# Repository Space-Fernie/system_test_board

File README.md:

# system_test_board
Test board for the Arietta G25 system

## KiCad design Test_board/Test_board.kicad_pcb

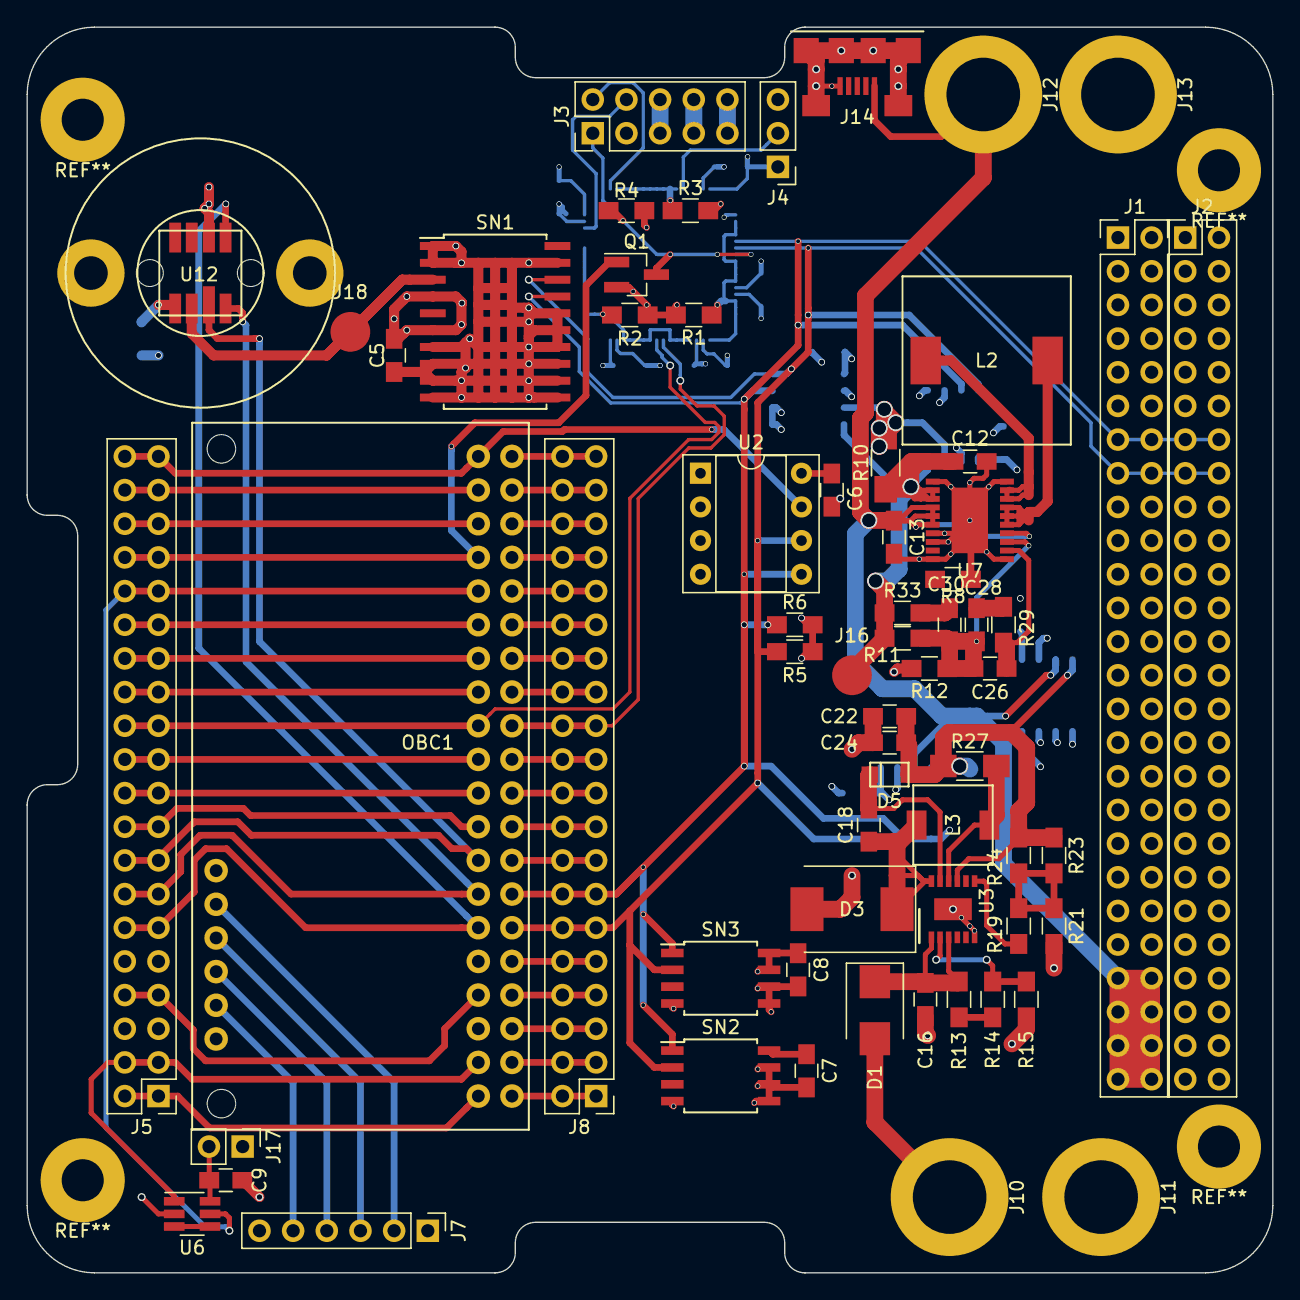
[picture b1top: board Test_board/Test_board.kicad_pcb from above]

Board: 4 copper layers, 94.0 x 94.0 mm, 80 parts (0 on the bottom side), 74 nets.

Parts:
C1, C2, C3, C4, C5, C6, C7, C8, C9, C14, C15, C16, C20, C21, C32, C33: 0.1uF; C_0805_HandSoldering
C12, C24: 100uF; C_0805_HandSoldering
C13: 47uF; C_0805_HandSoldering
C18: 1uF; C_0805_HandSoldering
C22: 10uF; C_0805_HandSoldering
C26: 12pF; C_0805_HandSoldering
C28: 680pF; C_0805_HandSoldering
C30: 47pF; C_0805_HandSoldering
D1: MBRS140; D_SMB
D3: MBRS340; D_SMC
D5: D; SOD-123FL
J1, J2: CONN_02X26; Pin_Header_Straight_2x26_Pitch2.54mm
J3: Conn_02x05_Odd_Even; Pin_Header_Straight_2x05_Pitch2.54mm
J4: Conn_01x03; Pin_Header_Straight_1x03_Pitch2.54mm
J5, J8: Conn_02x20_Odd_Even; Pin_Header_Straight_2x20_Pitch2.54mm
J7: Conn_01x06; Pin_Header_Straight_1x06_Pitch2.54mm
J10, J11, J12, J13: 4.19mmBananaJack; 4.19Banana
J14: USB_OTG; micro_usb_smd
J16, J18: TEST_1P; Measurement_Point_Round-SMD-Pad_Big
J17: Conn_01x02; Pin_Header_Straight_1x02_Pitch2.54mm
L2: 2.2uH; L-7443330220
L3: 6.8uH; L-SLF6028T-6R8M1R5-PF
OBC1: Arietta_G25
Q1: Q_NMOS_GSD; SOT-23_Handsoldering
R1, R2, R3: 4k7; R_0805_HandSoldering
R4: 4K7; R_0805_HandSoldering
R5, R6: 1k; R_0805_HandSoldering
R8: 90.9k; R_0805_HandSoldering
R9, R10: 20m; R_1206_HandSoldering
R11: 825k; R_0805_HandSoldering
R12: 182k; R_0805_HandSoldering
R13, R14, R15: 100k; R_0805_HandSoldering
R19: 179k; R_0805_HandSoldering
R21: 330k; R_0805_HandSoldering
R23, R24: 180k; R_0805_HandSoldering
R27: 50m; R_1206_HandSoldering
R29: 49.9k; R_0805_HandSoldering
R33: 6.49k; R_0805_HandSoldering
SN1: DS3232; SOIC-20W_7.5x12.8mm_Pitch1.27mm
SN2, SN3: DS1624; SOIJ-8_5.3x5.3mm_Pitch1.27mm
U1: STM32F303RE; LQFP-64_10x10mm_Pitch0.5mm
U2: 24LC256; DIP-8_W7.62mm_Socket
U3: LT3652; 12MSOP-E
U4, U9, U10, U11: INA219; SOIC-8_3.9x4.9mm_Pitch1.27mm
U6: MAX6730A; SOT-23-6_Handsoldering
U7: LTC3113; 20TSSOP-E
U12: MS5540C

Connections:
+3V3: C1.1, C2.1, C3.1, C4.1, C5.1, C6.1, C7.1, C8.1, C14.2, C15.2, C20.2, C21.2, C32.1, C33.1, J1.1, J1.2, J1.3, J1.4, J1.5, J1.6, J1.7, J1.8, J3.7, J3.8, J4.1, J5.5, J5.6, J7.6, J17.1, OBC1.5, OBC1.DP1, R4.1, R5.2, R6.2, R10.2, SN1.4, SN1.6, SN2.8, SN3.7, SN3.8, U1.13, U1.19, U1.32, U1.48, U1.64, U2.8, U4.5, U4.7, U9.5, U10.2, U10.5, U11.2, U11.5, U11.7, U12.5
+5V: J3.9, J3.10
+BATT: C13.1, J1.45, J1.46, J1.47, J1.48, J1.49, J1.50, J1.51, J1.52, J12.1, J14.1, R9.2, U7.4, U7.5, U7.6, U7.14, U9.7, U10.7
/32kHz: J18.1, SN1.3, U12.6
/ARM_MSTR_RST: J5.33, J5.34, OBC1.33, Q1.1
/ARM_RST: J3.1, Q1.3, R4.2, U1.7
/ARM_SWCLK: J3.2, U1.49
/ARM_SWDIO: J3.4, U1.46
/BARO_CLK: J5.11, J5.12, OBC1.11, U12.1
/BARO_MISO: J5.13, J5.14, OBC1.13, U12.8
/BARO_MOSI: J5.15, J5.16, OBC1.15, U12.7
/B_MCU_GND: R2.1, U1.20, U1.21, U1.22, U1.23, U1.26, U1.27, U1.28, U1.29, U1.30, U1.33, U1.34, U1.35, U1.36, U1.37, U1.38, U1.39, U1.40, U1.41, U1.42, U1.43, U1.44, U1.45
/DBG_MISO: J7.4, OBC1.DP3
/DBG_MOSI: J7.3, OBC1.DP4
/EEPROM_WP: J5.39, J5.40, OBC1.39, U2.7
/L_MCU_GND: R1.1, U1.2, U1.3, U1.4, U1.8, U1.9, U1.10, U1.11, U1.14, U1.15, U1.16, U1.17
/POWER/MPPT_IN: D1.2, J10.1
/POWER/MPPT_OUT: C22.1, C24.1, D5.2, R9.1, R23.1, R24.1, R27.1, U3.9, U9.8, U10.8
/POWER/VOUT3: C12.1, J16.1, R10.1, R11.1, R33.1, U4.8, U7.2, U7.3, U11.8
/SCL0: J1.15, J1.16, J2.15, J2.16, J8.11, J8.12, OBC1.12, R5.1, SN1.18, SN1.20, SN2.2, SN3.2, U1.6, U2.6, U4.4, U9.4, U10.4, U11.4
/SDA0: J1.13, J1.14, J2.13, J2.14, J8.13, J8.14, OBC1.14, R6.1, SN1.17, SN2.1, SN3.1, U1.5, U2.5, U4.3, U9.3, U10.3, U11.3
/T_MCU_GND: R3.1, U1.50, U1.51, U1.52, U1.53, U1.54, U1.55, U1.56, U1.57, U1.58, U1.59, U1.61, U1.62
/UART0_MISO: J8.23, J8.24, OBC1.24, U1.24
/UART0_MOSI: J5.23, J5.24, OBC1.23, U1.25
/WDT_KICK: J5.31, J5.32, OBC1.31, U6.5
/~OBC_RST: J5.3, J5.4, OBC1.3, U6.1
GND: C1.2, C2.2, C3.2, C4.2, C5.2, C6.2, C7.2, C8.2, C9.2, C12.2, C13.2, C14.1, C15.1, C16.2, C20.1, C21.1, C22.2, C24.2, C32.2, C33.2, D3.2, J1.18, J1.20, J1.22, J1.24, J1.26, J1.28, J1.30, J1.31, J1.32, J1.34, J1.36, J1.37, J1.38, J2.1, J2.2, J2.3, J2.4, J2.5, J2.6, J2.7, J2.8, J2.45, J2.46, J2.47, J2.48, J2.49, J2.50, J2.51, J2.52, J3.5, J3.6, J4.3, J5.9, J5.10, J7.1, J11.1, J13.1, J14.5, J14.6, OBC1.9, OBC1.DP6, Q1.2, R1.2, R2.2, R3.2, R8.2, R12.2, R15.2, R21.2, SN1.1, SN1.2, SN1.7, SN1.8, SN1.9, SN1.10, SN1.11, SN1.12, SN1.13, SN1.14, SN1.15, SN1.16, SN1.19, SN2.4, SN2.5, SN2.6, SN2.7, SN3.4, SN3.5, SN3.6, U1.1, U1.12, U1.18, U1.31, U1.47, U1.63, U2.1, U2.2, U2.3, U2.4, U3.6, U3.13, U4.1, U4.2, U4.6, U6.2, U7.1, U7.7, U7.8, U7.10, U7.11, U7.20, U7.21, U9.1, U9.2, U9.6, U10.1, U10.6, U11.1, U11.6, U12.2
unnamed: C9.1, J17.2, U6.6
unnamed: C16.1, D1.1, R13.1, U3.1, U3.3
unnamed: C18.1, D3.1, L3.2, U3.12
unnamed: C18.2, D5.1, U3.11
unnamed: C26.1, C28.1, C30.2, R11.2, R12.1, U7.13
unnamed: C26.2, R29.2, U7.12
unnamed: C28.2, R29.1
unnamed: C30.1, R33.2
unnamed: J4.2, U1.60
unnamed: J5.1, J5.2, OBC1.1
unnamed: J5.7, J5.8, OBC1.7
unnamed: J5.17, J5.18, OBC1.17
unnamed: J5.19, J5.20, OBC1.19
unnamed: J5.21, J5.22, OBC1.21
unnamed: J5.25, J5.26, OBC1.25
unnamed: J5.27, J5.28, OBC1.27
unnamed: J5.29, J5.30, OBC1.29
unnamed: J5.35, J5.36, OBC1.35
unnamed: J5.37, J5.38, OBC1.37
unnamed: J7.2, OBC1.DP5
unnamed: J7.5, OBC1.DP2
unnamed: J8.1, J8.2, OBC1.2
unnamed: J8.3, J8.4, OBC1.4
unnamed: J8.5, J8.6, OBC1.6
unnamed: J8.7, J8.8, OBC1.8
unnamed: J8.9, J8.10, OBC1.10
unnamed: J8.15, J8.16, OBC1.16
unnamed: J8.17, J8.18, OBC1.18
unnamed: J8.19, J8.20, OBC1.20
unnamed: J8.21, J8.22, OBC1.22
unnamed: J8.25, J8.26, OBC1.26
unnamed: J8.27, J8.28, OBC1.28
unnamed: J8.29, J8.30, OBC1.30
unnamed: J8.31, J8.32, OBC1.32
unnamed: J8.33, J8.34, OBC1.34
unnamed: J8.35, J8.36, OBC1.36
unnamed: J8.37, J8.38, OBC1.38
unnamed: J8.39, J8.40, OBC1.40
unnamed: L2.1, U7.18, U7.19
unnamed: L2.2, U7.15, U7.16, U7.17
unnamed: L3.1, R27.2, U3.10
unnamed: R8.1, U7.9
unnamed: R13.2, R14.1
unnamed: R14.2, R15.1, U3.2
unnamed: R19.1, R21.1, R23.2, R24.2
unnamed: R19.2, U3.7
unnamed: U6.3, U6.4

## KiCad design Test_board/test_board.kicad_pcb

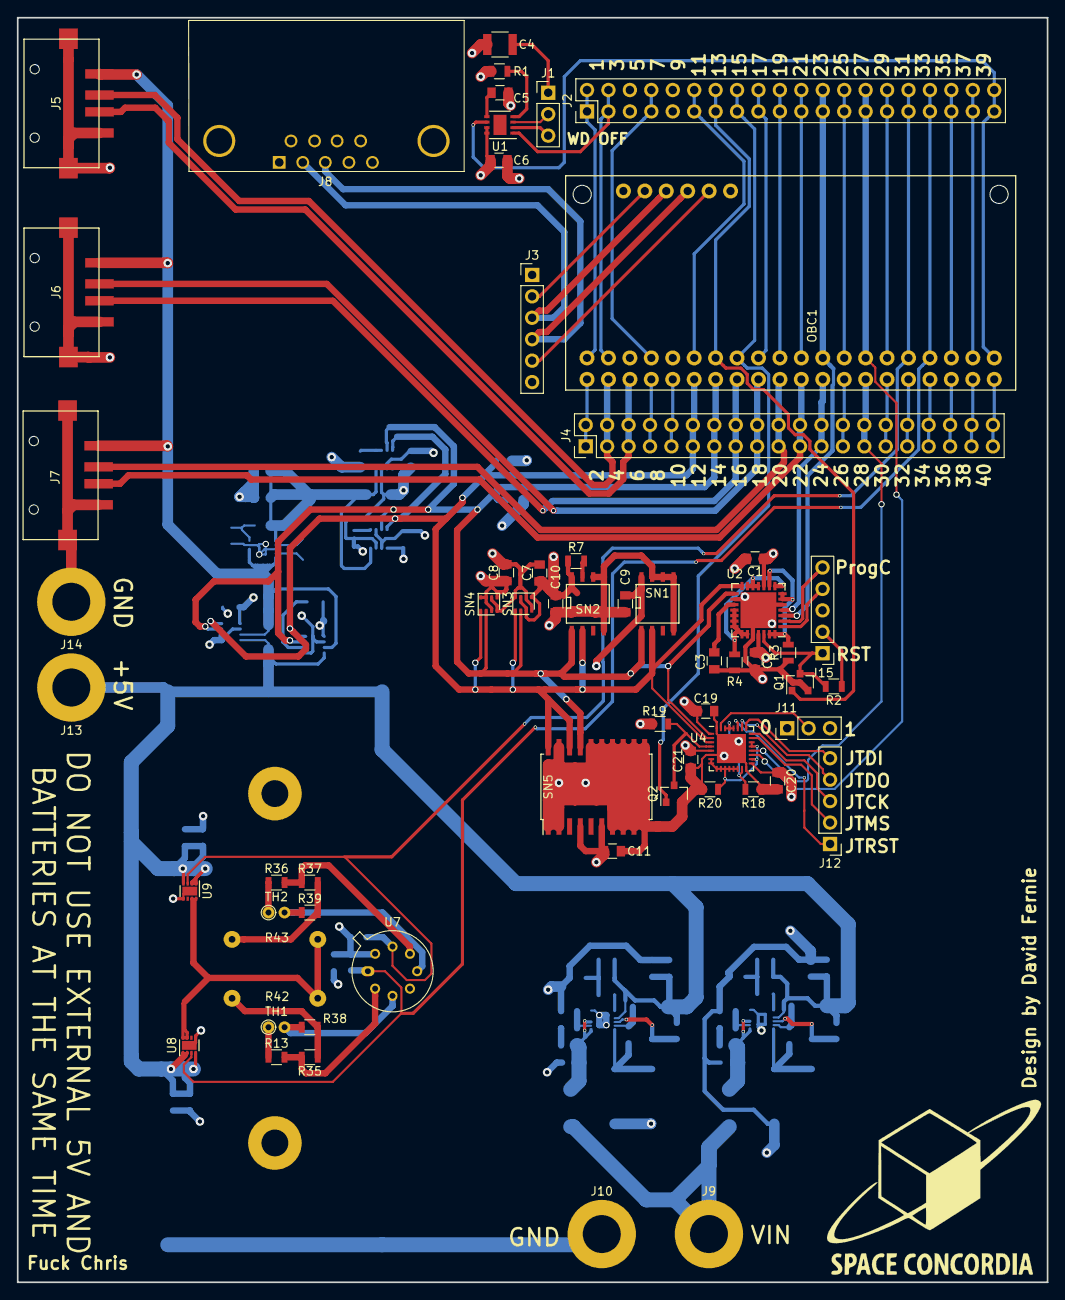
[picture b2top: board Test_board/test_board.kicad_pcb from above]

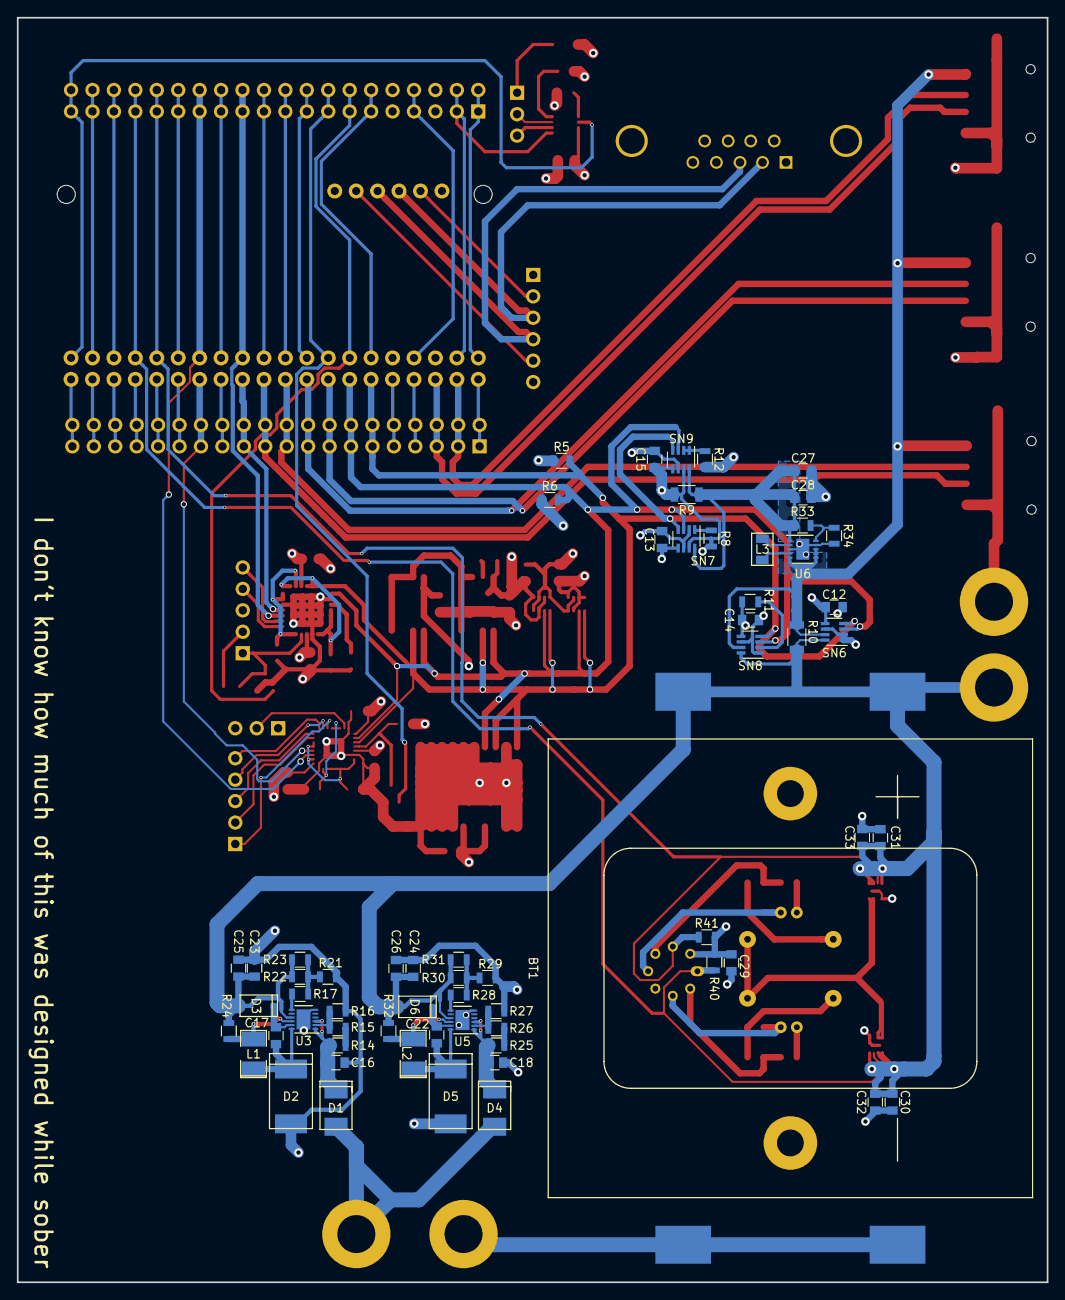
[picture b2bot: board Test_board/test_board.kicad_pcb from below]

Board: 4 copper layers, 122.0 x 149.9 mm, 124 parts (63 on the bottom side), 95 nets.

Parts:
BT1: Battery; Battery_Bracket_Small
C1, C2, C6, C7, C8, C9, C10, C11, C12, C13, C14, C15, C19, C20, C21, C29, C30, C31: 0.1uF; C_0805
C3, C16, C18, C23, C24: 10uF; C_0805
C4: 18uF; C_1210
C5: 0.2uF; C_0805
C17, C22, C32, C33: 1uF; C_0805
C25, C26: 100uF; C_0805
C27, C28: 22uF; C_0805
D1, D4: MBRS140; DO-214AA
D2, D5: MBRS340; SMC
D3, D6: D; SOD-323FL
J1, J11: CONN_01X03_MALE; Pin_Header_Straight_1x03_Pitch2.54mm
J2, J4: CONN_02X20; Pin_Header_Straight_2x20_Pitch2.54mm
J3: CONN_01X06; Pin_Header_Straight_1x06_Pitch2.54mm
J5, J6, J7: USB_A; USB_A_Board
J8: DB9_FEMALE; DB9FC
J9, J10, J13, J14: 4.19mmBananaJack; 4.19Banana
J12, J15: CONN_01X05; Pin_Header_Straight_1x05_Pitch2.54mm
L1, L2: 6.8uH; SMD-1210_Pol
L3: 1.5uH; SMD-1008
OBC1: Arietta_G25
Q1, Q2: 2N7002; SOT-23
R1, R33: 1M; R_0805
R2, R3, R4, R5, R6, R7, R8, R11, R12, R18, R19, R20, R40, R41: 4k7; R_0805
R9, R10: 20m; R_1206
R13, R35, R36, R37, R38, R39: 21k; R_0805
R14, R15, R16, R25, R26, R27: 100k; R_0805
R17, R28: 179k; R_0805
R21, R29: 330k; R_0805
R22, R23, R30, R31: 180k; R_0805
R24, R32: 50m; R_0805
R34: 178k; R_0805
R42, R43: HAP6948; WireConnection_0.80mmDrill
SN1, SN2: DS1624; SOIC-8-N
SN3, SN4: BMP280LGA; BMP280
SN5: DS3232; SOIC-20W_7.5x12.8mm_Pitch1.27mm
SN6, SN7, SN8, SN9: INA219; SOT-23-8
TH1, TH2: PT103J2; R_Axial_DIN0204_L3.6mm_D1.6mm_P1.90mm_Vertical
U1: MAX16056; DFN-8-1EP_3x3mm_Pitch0.65mm
U2: PIC24HJ128GP502-I/MM; QFN-28-1EP_6x6mm_Pitch0.65mm
U3, U5: LT3652; DFN-12-1EP_3x3mm_Pitch0.45mm
U4: STM32F302K8U6; QFN-32-1EP_5x5mm_Pitch0.5mm
U6: TPS63000; DFN-10-1EP_3x3mm_Pitch0.5mm
U7: LM193; TO-99-8_Window
U8, U9: TPS22965-Q1; DFN-8-1EP_2x2mm_Pitch0.5mm

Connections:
+3V3: C1.1, C2.1, C6.1, C7.1, C8.1, C9.1, C10.1, C11.1, C12.1, C13.1, C14.1, C15.1, C19.1, C20.1, C21.1, C29.2, J2.5, J2.6, J3.1, J11.3, J15.2, OBC1.5, OBC1.DP1, R1.1, R2.1, R5.1, R6.1, R7.1, R8.2, R9.2, R11.2, R12.2, R13.1, R19.2, R36.1, R40.1, R41.1, SN1.8, SN2.8, SN3.2, SN3.6, SN3.8, SN4.2, SN4.5, SN4.6, SN4.8, SN5.4, SN5.6, SN6.5, SN7.5, SN7.7, SN8.5, SN9.5, SN9.7, TH1.1, TH2.1, U1.7, U1.8, U2.10, U2.25, U4.1, U4.5, U4.17, U7.8
+BATT: BT1.1, C23.1, C24.1, C25.1, C26.1, C30.1, C31.1, C32.1, C33.1, D3.2, D6.2, J13.1, R10.1, R22.1, R23.1, R24.1, R30.1, R31.1, R32.1, SN6.8, SN8.8, U3.9, U5.9, U8.1, U8.2, U8.4, U9.1, U9.2, U9.4
/Arm_RST: J2.15, J2.16, OBC1.15, Q2.1
/DB_RX: J3.4, J8.3, OBC1.DP4
/DB_TX: J3.3, J8.2, OBC1.DP3
/JTCK: J12.3, U4.24
/JTDI: J12.5, U4.25
/JTDO: J12.4, U4.26
/JTMS: J12.2, U4.23
/JTRST: J12.1, U4.27
/M4_BOOT: J11.2, U4.31
/PIC_RST: J2.13, J2.14, OBC1.13, Q1.1
/Power/VCCP: D1.2, D4.2, J9.1
/ProgC: J15.5, U2.2
/ProgD: J15.4, U2.1
/Serial0_MISO: J4.23, J4.24, OBC1.24, U2.4
/Serial0_MOSI: J2.23, J2.24, OBC1.23, U2.3
/Serial1_MISO: J2.27, J2.28, OBC1.27, U4.19
/Serial1_MOSI: J4.27, J4.28, OBC1.28, U4.20
/USBA_D+: J4.5, J4.6, J5.3, OBC1.6
/USBA_D-: J4.3, J4.4, J5.2, OBC1.4
/USBB_D+: J4.15, J4.16, J6.3, OBC1.16
/USBB_D-: J4.17, J4.18, J6.2, OBC1.18
/USBC_D+: J4.21, J4.22, J7.3, OBC1.22
/USBC_D-: J4.19, J4.20, J7.2, OBC1.20
/Watchdog_pet: J2.39, J2.40, OBC1.39, U1.6
/~MCU_Reset: J15.1, Q1.3, R2.2, U2.26
/~RESET: J2.3, J2.4, OBC1.3, U1.1
GND: BT1.2, C1.2, C2.2, C3.2, C4.2, C5.2, C6.2, C7.2, C8.2, C9.2, C10.2, C11.2, C12.2, C13.2, C14.2, C15.2, C16.2, C18.2, C19.2, C20.2, C21.2, C23.2, C24.2, C25.2, C26.2, C27.2, C28.2, C29.1, C30.2, C31.2, C32.2, C33.2, D2.2, D5.2, J1.3, J2.9, J2.10, J3.6, J5.4, J5.5, J6.4, J6.5, J7.4, J7.5, J10.1, J11.1, J14.1, J15.3, OBC1.9, OBC1.DP6, Q1.2, Q2.2, R3.1, R4.2, R16.2, R18.2, R20.2, R21.1, R27.2, R29.1, R34.2, R35.2, R37.2, R38.2, R39.2, R42.2, R43.2, SN1.4, SN1.5, SN1.6, SN1.7, SN2.4, SN2.5, SN2.6, SN3.1, SN3.5, SN3.7, SN4.1, SN4.7, SN5.1, SN5.2, SN5.7, SN5.8, SN5.9, SN5.10, SN5.11, SN5.12, SN5.13, SN5.14, SN5.15, SN5.16, SN5.19, SN6.1, SN6.2, SN6.6, SN7.2, SN7.6, SN8.1, SN8.6, SN9.6, U1.2, U2.5, U2.16, U2.24, U2.29, U3.6, U3.13, U4.6, U4.16, U4.32, U4.33, U5.6, U5.13, U6.3, U6.9, U6.11, U7.4, U8.5, U8.9, U9.5, U9.9
Heater1: J2.33, J2.34, OBC1.33, R40.2, U7.1, U8.3
Heater2: J2.31, J2.32, OBC1.31, R41.2, U7.7, U9.3
unnamed: C3.1, U2.17
unnamed: C4.1, J1.1
unnamed: C5.1, U1.5
unnamed: C16.1, D1.1, R14.1, U3.1, U3.3
unnamed: C17.1, D3.1, U3.11
unnamed: C17.2, D2.1, L1.1, U3.12
unnamed: C18.1, D4.1, R25.1, U5.1, U5.3
unnamed: C22.1, D6.1, U5.11
unnamed: C22.2, D5.1, L2.1, U5.12
unnamed: J1.2, U1.3
unnamed: J2.1, J2.2, OBC1.1
unnamed: J2.7, J2.8, OBC1.7
unnamed: J2.11, J2.12, OBC1.11
unnamed: J2.17, J2.18, OBC1.17
unnamed: J2.19, J2.20, OBC1.19
unnamed: J2.21, J2.22, OBC1.21
unnamed: J2.25, J2.26, OBC1.25
unnamed: J2.29, J2.30, OBC1.29
unnamed: J2.35, J2.36, OBC1.35
unnamed: J2.37, J2.38, OBC1.37
unnamed: J3.2, OBC1.DP2
unnamed: J3.5, OBC1.DP5
unnamed: J4.1, J4.2, OBC1.2
unnamed: J4.7, J4.8, OBC1.8
unnamed: J4.9, J4.10, OBC1.10
unnamed: J4.25, J4.26, OBC1.26
unnamed: J4.29, J4.30, OBC1.30
unnamed: J4.31, J4.32, OBC1.32
unnamed: J4.33, J4.34, OBC1.34
unnamed: J4.35, J4.36, OBC1.36
unnamed: J4.37, J4.38, OBC1.38
unnamed: J4.39, J4.40, OBC1.40
unnamed: L1.2, R24.2, U3.10
unnamed: L2.2, R32.2, U5.10
unnamed: L3.1, U6.4
unnamed: L3.2, U6.2
unnamed: Q2.3, R19.1, U4.4
unnamed: R1.2, U1.4
unnamed: R3.2, U2.6, U2.7, U2.9, U2.27, U2.28
unnamed: R4.1, U2.8, U2.11, U2.12, U2.13, U2.18, U2.19, U2.20, U2.21, U2.22, U2.23
unnamed: R7.2, SN2.7
unnamed: R8.1, SN7.1
unnamed: R11.1, SN8.2
unnamed: R12.1, SN9.1, SN9.2
unnamed: R13.2, R35.1, U7.2
unnamed: R14.2, R15.1
unnamed: R15.2, R16.1, U3.2
unnamed: R17.1, R21.2, R22.2, R23.2
unnamed: R17.2, U3.7
unnamed: R18.1, U4.15, U4.28, U4.29, U4.30
unnamed: R20.1, U4.7, U4.8, U4.9, U4.10, U4.11, U4.12, U4.13, U4.14, U4.18, U4.21, U4.22
unnamed: R25.2, R26.1
unnamed: R26.2, R27.1, U5.2
unnamed: R28.1, R29.2, R30.2, R31.2
unnamed: R28.2, U5.7
unnamed: R33.2, R34.1, U6.10
unnamed: R36.2, R37.1, U7.6
unnamed: R38.1, TH1.2, U7.3
unnamed: R39.1, TH2.2, U7.5
unnamed: R42.1, R43.1, U8.7, U8.8, U9.7, U9.8
SCL0: J4.11, J4.12, OBC1.12, R5.2, SN1.2, SN2.2, SN3.4, SN4.4, SN5.18, SN5.20, SN6.4, SN7.4, SN8.4, SN9.4, U2.14, U4.3
SDA0: J4.13, J4.14, OBC1.14, R6.2, SN1.1, SN2.1, SN3.3, SN4.3, SN5.17, SN6.3, SN7.3, SN8.3, SN9.3, U2.15, U4.2
VCC: J5.1, J6.1, J7.1, R10.2, SN6.7, SN8.7, U6.5, U6.6, U6.7, U6.8
VDD: C27.1, C28.1, R9.1, R33.1, SN7.8, SN9.8, U6.1

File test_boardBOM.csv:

"Id,""Designator"",""Package"",""Quantity"",""Designation"",""Supplier and ref"",",,,,,,,,,,,,,,,,,
"1,""J5,J6,J7"",""USB_A_Board"",3,""USB_A""",,,,,,,,,,,,,,,
"2,""U1"",""DFN-8-1EP_3x3mm_Pitch0.65mm"",1,""MAX16056""",,,,,,,,,,,,,,,,,
"3,""J3"";""Pin_Header_Straight_1x06_Pitch2.54mm"";1;""CONN_01X06"";;;",,,,,,,,,,,,,,,,,
"4,""BT1"";""Battery_Bracket_Small"";1;""Battery"";;;",,,,,,,,,,,,,,,,,
"5,""C1",C2,C6,C7,C8,C9,C10,C11,C12,C13,C14,C15,C19,C20,C21,C29,C30,"C31"";""C_0805"";18;""0.1uF"";;;"
"6,""C3",C16,C18,C23,"C24"";""C_0805"";5;""10uF"";;;",,,,,,,,,,,,,
"7,""C4"";""C_1210"";1;""18uF"";;;",,,,,,,,,,,,,,,,,
"8,""C5"";""C_0805"";1;""0.2uF"";;;",,,,,,,,,,,,,,,,,
"9,""C17",C22,C32,"C33"";""C_0805"";4;""1uF"";;;",,,,,,,,,,,,,,
"10,""C25","C26"";""C_0805"";2;""100uF"";;;",,,,,,,,,,,,,,,,
"11,""C27","C28"";""C_0805"";2;""22uF"";;;",,,,,,,,,,,,,,,,
"12,""D1","D4"";""DO-214AA"";2;""MBRS140"";;;",,,,,,,,,,,,,,,,
"13,""D2","D5"";""SMC"";2;""MBRS340"";;;",,,,,,,,,,,,,,,,
"14,""D3","D6"";""SOD-323FL"";2;""D"";;;",,,,,,,,,,,,,,,,
"15,""J1","J11"";""Pin_Header_Straight_1x03_Pitch2.54mm"";2;""CONN_01X03_MALE"";;;",,,,,,,,,,,,,,,,
"16,""J2","J4"";""Pin_Header_Straight_2x20_Pitch2.54mm"";2;""CONN_02X20"";;;",,,,,,,,,,,,,,,,
"17,""J8"";""DB9FC"";1;""DB9_FEMALE"";;;",,,,,,,,,,,,,,,,,
"18,""J9",J10,J13,"J14"";""4.19Banana"";4;""4.19mmBananaJack"";;;",,,,,,,,,,,,,,
"19,""J12","J15"";""Pin_Header_Straight_1x05_Pitch2.54mm"";2;""CONN_01X05"";;;",,,,,,,,,,,,,,,,
"20,""L1","L2"";""SMD-1210_Pol"";2;""6.8uH"";;;",,,,,,,,,,,,,,,,
"21,""L3"";""SMD-1008"";1;""1.5uH"";;;",,,,,,,,,,,,,,,,,
"22,""OBC1"";""Arietta_G25"";1;""Arietta_G25"";;;",,,,,,,,,,,,,,,,,
"23,""Q1","Q2"";""SOT-23"";2;""2N7002"";;;",,,,,,,,,,,,,,,,
"24,""R1","R33"";""R_0805"";2;""1M"";;;",,,,,,,,,,,,,,,,
"25,""R2",R3,R4,R5,R6,R7,R8,R11,R12,R18,R19,R20,R40,"R41"";""R_0805"";14;""4k7"";;;",,,,
"26,""R9","R10"";""R_1206"";2;""20m"";;;",,,,,,,,,,,,,,,,
"27,""R13",R35,R36,R37,R38,"R39"";""R_0805"";6;""21k"";;;",,,,,,,,,,,,
"28,""R14",R15,R16,R25,R26,"R27"";""R_0805"";6;""100k"";;;",,,,,,,,,,,,
"29,""R17","R28"";""R_0805"";2;""179k"";;;",,,,,,,,,,,,,,,,
"30,""R21","R29"";""R_0805"";2;""330k"";;;",,,,,,,,,,,,,,,,
"31,""R22",R23,R30,"R31"";""R_0805"";4;""180k"";;;",,,,,,,,,,,,,,
"32,""R24","R32"";""R_0805"";2;""50m"";;;",,,,,,,,,,,,,,,,
"33,""R34"";""R_0805"";1;""178k"";;;",,,,,,,,,,,,,,,,,
"34,""R42","R43"";""WireConnection_0.80mmDrill"";2;""HAP6948"";;;",,,,,,,,,,,,,,,,
"35,""SN1","SN2"";""SOIC-8-N"";2;""DS1624"";;;",,,,,,,,,,,,,,,,
"36,""SN3","SN4"";""BMP280"";2;""BMP280LGA"";;;",,,,,,,,,,,,,,,,
"37,""SN5"";""SOIC-20W_7.5x12.8mm_Pitch1.27mm"";1;""DS3232"";;;",,,,,,,,,,,,,,,,,
"38,""SN6",SN7,SN8,"SN9"";""SOT-23-8"";4;""INA219"";;;",,,,,,,,,,,,,,
"39,""TH1","TH2"";""R_Axial_DIN0204_L3.6mm_D1.6mm_P1.90mm_Vertical"";2;""PT103J2"";;;",,,,,,,,,,,,,,,,
"40,""U2"";""QFN-28-1EP_6x6mm_Pitch0.65mm"";1;""PIC24HJ128GP502-I/MM"";;;",,,,,,,,,,,,,,,,,
"41,""U3","U5"";""DFN-12-1EP_3x3mm_Pitch0.45mm"";2;""LT3652"";;;",,,,,,,,,,,,,,,,
"42,""U4"";""QFN-32-1EP_5x5mm_Pitch0.5mm"";1;""STM32F302K8U6"";;;",,,,,,,,,,,,,,,,,
"43,""U6"";""DFN-10-1EP_3x3mm_Pitch0.5mm"";1;""TPS63000"";;;",,,,,,,,,,,,,,,,,
"44,""U7"";""TO-99-8_Window"";1;""LM193"";;;",,,,,,,,,,,,,,,,,
"45,""U8","U9"";""DFN-8-1EP_2x2mm_Pitch0.5mm"";2;""TPS22965-Q1"";;;",,,,,,,,,,,,,,,,
"46,""G***"";""logo"";1;"""";;;",,,,,,,,,,,,,,,,,

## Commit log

2017-09-18 Initial push, adding hardware and preliminary software
2017-09-18 Removed text file
2017-09-18 Found missing software files from first commit
2017-09-20 Added getTemp function to get all temperature readings from the compatible sensors. Underlying functions still need to be defined.
2017-09-21 Made the addresses passed to functions constants instead of variables for increased security.
2017-09-21 Added a reference document
2017-09-22 Deleted directories: Arietta G25, PIC24 Deleted files: All project files except for main.cpp originally for STM board Other: Software only contains one directory now, that holds the re purposed main;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
2017-09-22 Deleted PCB files, removed MCUs and 1 USB port from schematic, cleaned up schematic
2017-09-23 Developed program structure
2017-09-26 Changed MCU, generated new files, likely to change
2017-09-30 Another change to structure
2017-09-30 Started defining STM32F303RE component
2017-10-04 Updated schematic around MCU, defined comms pinout. Started setup of CAN bus connectors.
2017-10-10 Replaced TPS63000 with new IC and started wiring it. Started migrating previous libraries to new global Aleksandr library.
2017-10-14 Added component to library, fixed ground line for 3V3 converter.
2017-10-18 Added programming header to diagram. Changed drafting template
2017-11-02 Started V2.1, used template, found new programmable buck-boost converter
2017-11-03 Added temp, rtc, and mcu connections
2017-11-03 Wired the whole first sheet
2017-11-04 Wired most of power converters, only VC pins to wire
2017-11-07 Finished schematic
2017-11-08 Updated libraries, footprint assignments, and created protector for barometer
2017-11-09 Removed db9, created last footprints, finished assigning footprints, started pcb
2017-11-10 finished pcb
2017-11-16 mainly work on the barometer chamber
2017-11-22 project file modified
2017-11-23 Branched out for V3, started BBB cape for remote device
2017-11-24 Finished adding components and mapping connections for BBB cape
2017-11-24 Assigned some components
2017-12-14 Created step model of test board to try KiCad StepUp
